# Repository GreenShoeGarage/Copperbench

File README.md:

# COPPERBENCH
### A PCB workbench that feels like a PCB.

**Version 1.7.1 · Green Shoe Garage / Field Instruments · 18 September 2026**

[CaseBench export](docs/CASEBENCH-EXPORT.md) · [Editing and export review](docs/EDITING.md) · [Pan the view](#new-in-v163--pan-the-view) · [Compact polarity](#new-in-v162--compact-polarity-markings) · [Quieter workbench](#new-in-v161--quieter-workbench) · [Modules & circuit blocks](#new-in-v16--modules-and-editable-circuits) · [Controller carriers](#controller-carriers) · [Everyday maker parts](#everyday-maker-parts) · [Polarity & silkscreen fix](#polarity-and-silkscreen) · [Power & ground planes](#power-and-ground-planes) · [Create vias](#create-vias) · [HATs & shields](#hats-shields-and-carriers) · [Get started](#start-here) · [Publish to GitHub](docs/GITHUB.md) · [Deploy](docs/DEPLOYMENT.md) · [Verification](docs/TESTING.md) · [Contribute](CONTRIBUTING.md)

Put down a board. Place recognizable parts. Connect their leads. Shape the copper. Add your markings. Inspect the files you will send for fabrication.

COPPERBENCH is a local-first, two-copper-layer PCB layout app with an editable, depth-rendered 3D workbench. **COPPERBENCH is the working title for this release.** The physical bodies are representative; pad geometry and the electrical connection model—not rendered pixels—drive routing, checking and manufacturing export.

## New in v1.7.1 — CaseBench board JSON

Click the **▾ beside Export board → CaseBench JSON**, or use **Board →
CaseBench JSON**. Review the dimensions and component/hole counts, then choose
**Download CaseBench JSON**. In CaseBench, import it as a CopperBench board.
No upload or service is involved.

The download uses native **`app: "COPPERBENCH"`, schema 5, `units: "mm"`**.
Board shape/thickness, both-side components, local pads, active mounting holes,
slots, cutouts, vias, module/carrier metadata and placed block records are retained.
It does not flatten, move, mirror or rescale the geometry; the CaseBench importer
owns the conversion into enclosure coordinates. Representative module body height
already includes its modeled stack and is not increased again.

The default board snapshot omits artwork, image assets, saved baseline and unused
circuit-block templates. **File contents & options → Include project extras**
retains those too. Keep **Save JSON** for complete editable-project backups.
Unrouted nets or stale copper fills do not block this enclosure handoff. Pending
placement/edit proposals and changes after review do block downloading an obsolete
snapshot. File size and known CaseBench native-adapter bounds are preflighted.

No project-format migration or new runtime dependency. The target CaseBench app
was not available locally for an end-to-end import test; the native contract and
geometry preservation are tested, not physical enclosure fit. See the
[handoff guide](docs/CASEBENCH-EXPORT.md) and [verification record](docs/TESTING.md).

## New in v1.7 — editing and export review

Select the object you intend to edit with **Parts / Copper / Markings / Board
features** filters. Click a crowded location and press **]** to cycle overlapping
objects. Slide trace segments, move/insert/remove corners, replace a section and
clean redundant bends. Widths can target one segment, a trace, touching copper or
an explicitly selected whole net.

Turn on **Drag connected** for a rule-checked component/via move. Supported
centered endpoint attachments follow on their existing layers. A blocked or
unsupported move leaves the original board intact. This is deliberately limited:
no push-and-shove, locked attachments, through-middle junctions or pour-net moves.
Both manual trace changes and connected moves use **Keep edit / Cancel** previews
and one-step undo; they are not live, silent changes to the underlying copper.

**Position marks** moves printed reference or polarity groups without moving pads.
Export review checks actual generated files against the reviewed revision, compares
drills, and reports sampled silk clipping. The ZIP now includes a revision manifest.
Unreadable local saves or detected other-tab changes pause autosave until explicitly
resolved; **Log → Recovery snapshots** can download both copies first.

All **193 parts, six circuit blocks and schema-5 projects** are retained. No new
runtime dependencies. Save a JSON backup before updating; replace the complete
static folder or portable HTML. See the [editing guide](docs/EDITING.md),
[verification record](docs/TESTING.md) and [qualification boundaries](docs/QUALIFICATION.md).
Native browser navigation and the optional third-party parser gate were **blocked**
in the release environment, not counted as passed. No manufacturer acceptance or
physical fabrication is claimed.

## New in v1.6.3 — pan the view

**Pan** now has a labelled button beside **Fit**, in all three views and on both
board faces. Toggle it with **P**, then drag anywhere on the canvas without moving
parts. **Space-drag** or **middle-drag** pans temporarily, including mid-trace.

Scroll pans while Pan is on; Ctrl/Command-scroll still zooms. On a touchscreen,
one finger in Pan or two fingers in any tool moves the view, with pinch zoom
anchored beneath the gesture. **Fit / Home** brings the board back to centre.

Selection, pending placements, unfinished traces, undo history and manufacturing
geometry are preserved. There is no new idle instruction banner, no dependency,
and no project-format change (schema 5). The 193 parts, six circuit starters,
planes, vias and compact printed polarity markings are retained.

[Navigation controls and details](docs/NAVIGATION.md) · [Verification](docs/TESTING.md)

## New in v1.6.2 — compact polarity markings

Removed the always-on A/K billboards and the expanded name badges. The idle
workbench shows the actual small printable symbols. Selection, hovering a lead,
or routing exposes **9-pixel pin tags** placed outside projected component bodies,
including their height when the board is tilted. Full terminal names remain in
the tooltip, inspector and pin table; the small tags still select their actual pins.

**A/K and +/− are real silkscreen**, enabled by default, with 0.9 mm default print
height and 0.16 mm stroke. A direct **Print polarity on silkscreen** checkbox is
available in the selected-part inspector. **Polarity & pin roles → Compact print
defaults → Apply polarity labels** restores the small enabled print settings.
Screen tags and printed sizes are independent. Four-lead RGB LEDs now receive
separate, pin-ordered markings instead of overprinted A/K pairs.

Existing explicit print settings and opt-outs are preserved. Back up your JSON,
inspect **Fabrication → Top silk only / Bottom silk only**, and regenerate the
manufacturing ZIP. Schema remains **5**. No pad, pin number, net, copper, or drill
geometry was changed by the label redesign. Read the [polarity guide](docs/POLARITY_AND_SILKSCREEN.md)
and [verification record](docs/TESTING.md). The [example board](examples/compact-polarity.json)
is an unconnected illustration, not a complete circuit.

## New in v1.6.1 — quieter workbench

The board is the focus. Removed the welcome overlay, canvas slogans, repeated
instructions and duplicate empty-inspector statistics. Search is first in the
parts drawer; a category selector replaces the filter-chip wall, and compact
catalog buttons replace long promotional labels. Additional block and footprint
actions live under **Library tools**.

The idle Select tool has no instructional sentence. Active tools display a short
next-step hint; the **?** beside the tool name opens complete instructions without
cancelling the operation. Header **?** or **H** opens the full guide and shortcuts.
Autosave, polarity, error/warning counts, clearance failures, confirmation dialogs
and fabrication-export gates remain visible and operational. Native schema 5,
the 193 parts and all six circuit blocks are unchanged.

**Upgrade:** save a JSON backup and replace the complete hosted app folder, or
replace the standalone HTML. No new schema migration is needed for v1.6 projects.
See the [interface guide](docs/QUIET_WORKBENCH.md) and [verification record](docs/TESTING.md).

## New in v1.6 — modules and editable circuits

**Five specific module interfaces and six reusable circuit starters.** The component
library now has **193 entries**; circuit blocks are a separate collection of editable
parts, copper and net intent—not six opaque additional footprints.

| Mount a purchased module | Build and edit a circuit |
|---|---|
| Adafruit BME280 original non-QT, DS3231 original eight-pin RTC, 0.96-inch OLED STEMMA QT, TB6612 breakout, and MPM3610 3.3 V module. | LED indicator, button with pull-up, I²C pull-ups, supply decoupling, DC-input topology, and RC signal filter. |
| Named pins, source CAD/blob references, optional mounting holes, adjustable assumed underside gap, and distinct representative 3D bodies. | Pre-routed internal copper, editable values, explicit external ports, fresh nets per insertion, one-step undo, group transforms and fresh-net copies. |

Open **Parts → Modules** or **Parts → Circuit blocks**. Module templates
place the mating headers on your carrier; the illustrated host electronics do not
leak into fabrication files. Block placement checks for new copper conflicts while
preserving intentionally unrouted connections as design findings.

Select a block member to **select the whole block, move/rotate/flip it with its
copper, copy it with fresh nets, export it, or detach the grouping**. Save selected
components/traces/vias to a project-local personal library; import and export
`.copperblock.json` files for sharing. GND is not silently shared between copies.

**Back up first. Native JSON now writes schema 5**, reading schemas 1–4 without
replacing existing embedded footprints. Older app versions reject the new format.
Source-referenced module interfaces and circuit examples are **not physically fit
tested, simulated or electrically certified**. KiCad retains ordinary supported
geometry/nets, not module metadata, block grouping or your personal library.

[Module and block guide, source ledger and limits](docs/MODULES_AND_BLOCKS.md) ·
[Verification](docs/TESTING.md) · [Compatibility](docs/COMPATIBILITY.md)

## Controller carriers

**v1.5 added 18 header-mounted interfaces for nine host selections; all are retained.** Start with **Parts → Controllers** or use
**Examples → Controller carriers**. Choose Pico, Pico 2, Pico W, Pico 2 W, classic
Nano A000005, ESP32-DevKitC V4 with WROOM-32E, the classic Feather interface,
original XIAO RP2040 or XIAO ESP32C3. Each has a carrier and an add-on variant;
Feather's add-on is a FeatherWing-style mating pattern.

**Carrier clearances & fit** edits the assumed stack gap, USB/access projections,
and attached two-face antenna guards where applicable. Copper guards affect
manual routing, vias, automatic routing and plane fills. They follow moves,
rotations and flips; hiding their overlay never disables them. A guard override
requires a saved reason and remains a warning. XIAO ESP32C3 uses an external
antenna reference; generic Feather cannot imply a radio-specific keepout.

The footprint contacts are routable, named and included in manufacturing exports.
Host drawings and clearance overlays are editor-only. Optional mounting holes
are real NPTH geometry; ESP32 and XIAO do not receive invented holes. Existing
parts, optional Uno ICSP, vias, planes, polarity labels and repaired silk exports
are retained.

**These are nominal source-referenced templates, not fit-tested assemblies.**
The RF defaults are suggested projections, not complete manufacturer-qualified
clearances. Header-to-edge offsets, holes, connector drill size, stack gap and
cable access require actual-board review. The generic Feather entry provides
common aliases, not universal MCU pin mappings. Direct castellated mounting is
not included. See the [carrier guide and source/geometry qualifications](docs/CARRIERS.md).

**Native JSON now writes schema 5; older editors will reject it.** Schemas 1–4
open without silently replacing embedded footprints. Back up before upgrading.
KiCad exports active RF guards as independent keepouts, not linked constraints;
retain JSON as the lossless master. [18 starter projects](examples/carriers/) are
included. These starters are interfaces, not complete functioning circuits.

## Everyday maker parts

**v1.4 adds 134 variants in 17 families, for 170 total library entries at that release.** Choose
**Parts → Maker parts**, select a family and exact variant, and place it
on the board. The drawer groups variants instead of listing hundreds of similar
cards; search finds device names, manufacturers and pin functions directly.

Connectors include header/socket/right-angle variants, screw terminals, JST
PH/XH/SH, a Qwiic/STEMMA QT preset, and a selected GCT USB4085 USB-C connector.
Controls include switches, potentiometers and an encoder. Power/assembly entries
include regulators, protection templates, transistors, a relay, fuses, LEDs,
jumpers and test loops. Named NE555, LM358, SN74HC595, MCP23017 and ULN2803C package
entries expose actual pin functions instead of anonymous pad numbers.

**Functional pin names** edits labels without changing pin numbers or nets.
Selected parts show editor-only captions; existing A/K and +/− polarity symbols
remain real printed silkscreen. **Part reference, notes & pin-map CSV** exposes
source links, cautions and review status. Internally common terminals assigned to
different nets produce a blocking finding—not an automatic merge.

**Arduino Uno R3 now has an optional ICSP 2×3 header.** Enable it in the platform
chooser or on an existing Uno part. Its six contacts are appended without changing
the original 32 pins or connections. Existing default templates stay unchanged.

**Important:** 134 variants does not mean 134 physically qualified purchased
components. Some entries are named-device references; others are explicitly
nominal parametric templates. Review the exact part, geometry, connector direction,
pin mapping and drill/slot capability before fabrication. USB connectors and
regulators are parts, not complete supporting circuits. No physical fit or
manufacturer approval is claimed.

Try **Examples → Everyday maker sampler**, or open
[`everyday-maker-sampler.json`](examples/everyday-maker-sampler.json). The example
is a layout sampler, not an electrically complete circuit. See the
[Maker Parts guide](docs/MAKER_PARTS.md) and [catalog index](docs/MAKER_CATALOG.md).
v1.6 uses schema 5 and retains these embedded footprints and checks. Back up before upgrading.

## Polarity and silkscreen

**v1.3.1 fixes an export defect that could clear the entire silkscreen. Open your
native project in this version and regenerate its manufacturing ZIP before
ordering. Previously downloaded Gerbers are not repaired by updating the app.**

Diodes and LEDs now identify **A · Anode** and **K · Cathode**. Polarized radial
capacitors identify **+ · Positive** and **− · Negative**. Small tags appear while
selecting or wiring, stay outside projected component bodies, and never expand
into full-name badges. Full names remain in tooltips, the inspector and pin table.

Select a component and open **Polarity & pin roles** to assign roles to custom or
imported pins, toggle printing, or adjust symbol size, clearance and offsets.
Printed A/K or +/− symbols follow the component's rotation and board face and are
included in the Gerbers. Hiding the reference label does not hide polarity marks;
disabling printed polarity does not remove the contextual pin tags. No operation
silently swaps pin numbers or reassigns nets. Unknown/numeric pin roles are not
guessed from net names or body appearance.

**Fabrication → Top silk only / Bottom silk only** shows the generated files
without component bodies or editor badges. Source text, part references,
polarity marks, drawing tools and converted images survive export, while pad
openings, holes, cutouts and off-board artwork are still cleared.

The old writer incorrectly treated nested Gerber contours like an even-odd hole.
The old viewer and Python test reader repeated that error. All three are fixed;
new tests explicitly reproduce the blank old output and require union semantics.
The clipping replacement uses individual exterior trapezoids, not another nested
frame. See the [fix guide](docs/POLARITY_AND_SILKSCREEN.md) and
[verification record](docs/TESTING.md). **No external CAM acceptance or physical
fabrication is claimed.** v1.6 writes schema 5; save a JSON backup first.

## Start here

**The simplest edition is `COPPERBENCH-portable.html`.** Open that file in a desktop browser. It includes the complete app, component definitions, ZIP support and routing/checking worker source. There is no build step, account, CDN or required internet service.

Alternatively, keep the static app folder together and open `index.html`. A local server is useful where browser file-origin policies interfere with local storage or workers:

```sh
cd copperbench
python3 tools/serve.py
```

Open `http://127.0.0.1:8000/`. Python is optional for using the portable HTML. Node and Python test dependencies are only needed for development/testing.

**Save JSON is your independent backup.** Autosave uses browser-local storage, which can be disabled, full, cleared, or unavailable for local files. A saved-state LED reports persistence status; a failed save does not disable JSON export. Downloaded JSON contains placed footprints and embedded source images.

The release uses a real Chromium DOM/canvas/worker harness with a storage test double and intercepted download blobs. Unrestricted `file://` launch, origin-backed storage, actual download navigation, and hosted service-worker installation were **not** directly verified. Read the [verification record](docs/TESTING.md) for exact coverage instead of treating “offline-capable” as a claim that every browser environment has been tested.

## Power and ground planes

Open **Planes → Bottom ground · top routing**. Or assign a net independently to
**Top copper** and **Bottom copper**. No whole-board polygon drawing is needed.
The plane follows the outline and automatically refills after copper edits.

Choose **Connect a lead to GND** (or your selected net), click a component lead,
then review **Keep connection / Discard**. Through-hole and same-face pads use
existing direct contact when possible. Opposite-face surface-mount pads receive
a short trace and nearby through via, or reuse a suitable existing via. Inspector
pin buttons and picked multi-lead groups expose the same workflow.

**No silent net merges.** Unassigned leads adopt the target net only on acceptance;
a lead on a different net is blocked. Connection status uses real filled-copper
paths, not names. Split planes, stranded leads and stale fills remain visible.
Changing plane assignment does not relabel pins or existing copper. Manual zones
are preserved. New traces carve clearance through managed pours and may split them.

Thermal pad connections, solid via connections, per-face settings, a view-only
hide-fill control, manual refill and one-step undo are included. The local helper
is non-exhaustive and the existing fill engine is conservative/cell-derived.
**Native saves use schema 5 in v1.6; back up older projects before upgrading.**

[Plane workflow and limitations](docs/PLANES.md) · [Verification](docs/TESTING.md)

## Create vias

Click **＋ Via** beside the trace-width control, choose **Place via** in the Nets
panel, or press **Shift+V**. The inspector shows the via's net, copper-pad diameter,
drill diameter and solder-mask setting. Click the board to place; keep clicking
to place more. **Esc** leaves the tool.

**Auto / from touching copper** takes the net from the copper beneath the via,
including the opposite face. A placement joining different nets is blocked.
For an empty area, choose a named net or create one. Unassigned vias remain
editable but produce a blocking finding before ordinary manufacturing export.
The green/red preview checks the selected rule profile on both copper layers.

| Preset | Copper pad diameter | Drill diameter |
|---|---:|---:|
| Compact | 0.70 mm | 0.30 mm |
| Standard | 0.90 mm | 0.40 mm |
| Large | 1.20 mm | 0.60 mm |

Enter custom dimensions as needed. Presets are geometric conveniences, not
current ratings or universal fabrication approval. The inspector displays the
annular ring and rejects dimensions below the active profile limits.

**During manual tracing**, press **V** at the cursor, or click **Via → other side**
and then the board. The incoming trace and via are one undoable edit, and the
route continues on the opposite layer. A rejected placement leaves the trace
and board unchanged. Traces can start or finish on existing vias and copper.

**To edit**, leave placement mode and select the via—even at a trace endpoint.
Change its position, net, diameters, mask coverage or lock state. **Manage vias**
in the Nets panel lists all vias. Moving a connected via does not stretch the
attached traces; resulting disconnections are reported.

A via is real copper on **both faces** and **one plated Excellon drill**, not an
NPTH mounting hole. **Tent both sides** omits its solder-mask openings on both
faces; it does not request hole filling or guarantee a physically sealed hole.
Native JSON preserves all settings. The bounded KiCad exchange preserves via
geometry/nets, but not per-via tenting or locks; the app warns before that export.

See the [via guide](docs/VIAS.md), [format limits](docs/COMPATIBILITY.md), and
[verification record](docs/TESTING.md). No manufacturer upload or physical test
board is claimed for this release.

## HATs, shields and carriers

**Parts → HATs & shields** opens the new form-factor workflow. Select
Raspberry Pi 40-pin, Arduino Uno R3, or Arduino MKR 28-pin; choose an add-on above
the host or a carrier below it. **Start new board** creates an outlined blank
with the mating pattern and optional mounting holes. **Place headers on current
board** adds only the interface, preserving your existing layout.

There are **six new Parts → Platforms entries**, one add-on and one carrier
variant per family. Pins are directly routable, with physical contact IDs and
signal aliases in the inspector, hover tooltip and searchable pin table. No pins
are silently joined just because their signal names match. Export a pin-map CSV
from the selected interface's inspector.

| Family | Included geometry | Important boundary |
|---|---|---|
| Raspberry Pi 40-pin | 2×20 connector; physical/BCM aliases; 65×56 mm legacy-style add-on blank; four optional mounts | Not Pico, Compute Module, original 26-pin Pi, or automatic HAT/HAT+ compliance. |
| Arduino Uno R3 | All 32 perimeter contacts; grouped banks; exact 4.064 mm D8–D7 gap; classic-outline starter | ICSP 2×3 is optional. Not a blanket Uno R4 / clone compatibility claim. |
| Arduino MKR 28-pin | Two 14-pin rows; 2.54 mm pitch; 20.32 mm row spacing; shield and carrier roles | WiFi 1010 reference envelope/nominal offsets. Check the actual MKR variant, antenna and power pins. |

The compound pattern starts **locked** in a new template. Uncheck **Lock placement**
in the inspector to move, rotate or flip it. Its included mounting holes move
with it. **Host reference & mounting holes** toggles the reference illustration,
editor-only captions and real NPTH holes independently. The host picture is not
a collision/clearance model and does not export fake host circuitry.

All dimensions are **nominal, review-required**. Check the purchased connector,
actual host, standoffs, power direction and clearances. See the detailed
[form-factor reference and source register](docs/FORM_FACTORS.md).

**Project format:** v1.6 reads schema-1/2/3/4 projects and writes schema 5. Older apps
reject the new schema instead of silently dropping block records or attached carrier constraints.
Keep the original JSON backup before upgrading. Native JSON preserves platform
aliases, linked mounting holes and plane behavior. KiCad subset exchange retains
supported geometry, not all application metadata.

## Try the complete workflow

1. Open **Examples → Little light**, or open `examples/little-light-routed.json` to inspect the completed routing example. Choose **Fresh start** for an empty board.
2. In **Parts**, click a part and click the board, or drag it from the drawer. **R** rotates; **F** moves the selected component to the opposite face. The inspector has exact position, angle, value and pin assignments.
3. Choose **Connect** (**A**), pick two or more leads belonging on one net, then choose **Preview wire → Keep copper**. Copper is not committed until accepted. Different-net assignments require an explicit merge decision. **Pair connectors** creates separate mapped connections instead of shorting an entire selection together.
4. Choose **Trace** (**T**) for manual routing. Set the visible trace width, click a lead, via or existing trace, add waypoints and click the destination. **V** inserts a through via at the cursor during a route, switches to the opposite layer and continues. The visible **Via → other side** button instead arms the next click. **Enter** finishes an open route; **Esc** cancels unfinished work.
5. Use **Board** to adjust size/shape, draw polygon boundaries, add mounting holes, slots or cutouts. Resizing changes the boundary, never the dimensions of parts or copper.
6. Use **Mark** for text, lines, boxes, ellipses or image conversion. Imported raster/SVG images become explicit silkscreen rectangles, with the source raster retained for reprocessing. Use **Check design**, then **Fabrication**, then **Export board**. Review the actual manufacturer preview before ordering.

For easy whole-board pours, use **Planes**. For manual local pours, draw a **Zone** (**Z**), assign its net and refill. Zones use conservative, vectorized cell fills, with optional thermal reliefs and island removal. Copper/board edits and project imports invalidate pours; stale pours block manufacturing export, even when diagnostic export is selected.

## Established workbench features

| Area | Implemented |
|---|---|
| Physical workbench | Shaded, depth-buffered representative 3D bodies; tilt, orbit, zoom, pan, top/bottom views, x-ray and pin picking. |
| Parts | 193 entries including five module interfaces, 18 controller interfaces and 134 maker variants, named device pins, source notes, optional Uno ICSP, footprint wizard, exact pad editing in Advanced mode, rotate/flip, duplicate, lock, pin table. |
| Circuit blocks | Six routed starters, explicit external ports, isolated-net insertion/copy, editable members, group transforms, project-local library and standalone block JSON. |
| Modules | Five source-identified mating interfaces with named pins, optional mounting holes, reference-only 3D bodies and nominal stack-gap review. |
| Carriers | Nine added host selections, carrier/add-on templates, attached two-face RF guards, access references and editable stack-gap assumptions. |
| Connection intent | Explicit nets independent of drawn copper, visible unrouted connections, guarded net merges, connector-pair mapping. |
| Routing | Width-controlled manual polylines, selected two-/multi-pin A* proposals, keep/reject preview, through vias, cancellable worker jobs. |
| Vias | Visible repeat-placement tool, net inheritance, pad/drill presets and exact sizes, mask tenting, live clearance checks, editable/lockable objects and a management table. |
| Planes | Per-face net assignment, bottom-ground preset, board-following auto-refill, checked lead-to-plane previews, local stub/via helpers, real-region status and split-plane findings. |
| Board/copper | Rectangular, rounded, circular/elliptical and polygon outlines; polygon cutouts/keepouts; holes/slots; thermal and solid cell-derived copper fills. |
| Markings | Drafting text, basic shapes, mirror/rotate, threshold/invert/cleanup image conversion, original-image reprocessing, minimum-feature and clipping warnings. |
| Inspection | Geometry/connectivity findings with severity and evidence, footprint-verification flags, assumptions/evidence register, baseline comparison, HTML/print review report. |
| Files | Native JSON/project ZIP, Gerber X2 or RS-274X compatibility output, Excellon drills/G85 slots, optional paste, BOM CSV, SVG output, bounded KiCad interchange. |
| Workspace | Undo/redo, autosave and recovery snapshots, Easy/Advanced modes, light/dark/high-contrast themes, collapsible drawers/inspector, responsive layout. |

**Bench, Copper and Fabrication are views of one design.** The Fabrication view reads the generated Gerber/Excellon text rather than redrawing the project and calling that verification.

## Manufacturing: inspect before ordering

Export produces front/back copper, mask and silkscreen, an outline/cutout Gerber, and the applicable plated/non-plated drill files. Optional paste layers are available. Coordinates share one physical origin; bottom manufacturing files are not mirrored. The native editor uses millimetres and a top-left, Y-down coordinate system; export converts Y to a lower-left, Y-up system.

An editable OSH Park two-layer rule profile is included with its source and verification date. Manufacturer limits can change. Confirm the selected service, current rules, upload interpretation and preview before placing an order.

**This release has not been submitted to OSH Park, checked by an external CAM product, or physically fabricated.** Its exports passed JavaScript read-back and a separate Python/Shapely geometry regression for a golden test coupon. That is useful evidence, not manufacturer approval or a guarantee that an arbitrary circuit will work.

Generic footprints are marked **unverified** until you check the purchased part's mechanical drawing, pin order and recommended land pattern. Width presets are dimensions, not current ratings. A zero-error layout is not a circuit-function, high-voltage, RF, thermal or regulatory certificate.

## Deliberate boundaries

This is not a complete replacement for an industrial EDA suite. Two copper layers and through vias are supported; multilayer stackups, blind/buried vias, simulation, controlled impedance and push-and-shove routing are not. Automatic routing is selected-connection assistance, not guaranteed full-board optimization. Moving a part leaves existing copper in place and exposes any resulting broken connections.

Copper pours are cell-derived vector rectangles, not a general exact polygon-boolean engine. Arcs imported from KiCad are flattened to polylines. Representative component bodies are not STEP models or mechanical collision certification. The silkscreen alphabet is a bundled geometric drafting alphabet rather than arbitrary typography.

KiCad import/export is an **explicit feature subset**, not general round-trip compatibility. Important unsupported manufacturing features stop import; permitted simplifications are reported. Imported board artwork is flattened; standalone footprint placement imports pads/body, not original footprint artwork. External 3D assets are not fetched. See [format compatibility](docs/COMPATIBILITY.md).

## GitHub-ready repository

Extract the source ZIP and put the **contents of the `copperbench` folder** at
your repository root. Include hidden files and folders. There is no preconfigured
remote, account name, domain, Git history or secret in the package.

The repository includes an illustrated README, MIT and dependency notices,
contribution/security guides, issue and pull-request templates, pinned test
dependencies, a lockfile, source integrity checks, deterministic release
packaging and three GitHub Actions workflows:

| Workflow | Behavior |
|---|---|
| **CI** | Source/asset checks, packaging regressions, engine tests, independent manufacturing geometry and the Chromium interaction harness. |
| **Deploy GitHub Pages** | Manual deployment after Pages setup; optional automatic deployment from `main` with `ENABLE_PAGES=true`. |
| **Draft release** | A matching pushed version tag creates a draft with source/static ZIPs, portable HTML and SHA-256 checksums after CI. |

[GitHub setup](docs/GITHUB.md) explains the initial push and release tags.
[Deployment](docs/DEPLOYMENT.md) covers local launch, Pages and an ordinary static
host. These workflow files are prepared locally; no remote Actions run or live
site is claimed.

```text
copperbench/
├── index.html                 Ready-to-run static entry point
├── COPPERBENCH-portable.html   Self-contained offline edition
├── styles.css                 Responsive themes and layout
├── src/                       PCB model, geometry, renderer, UI and exporters
├── vendor/                    Bundled JSZip and its original license
├── examples/                  Starter designs and regression coupon
├── docs/                      Screenshots, compatibility, guides and evidence
├── tests/                     Engine, browser, manufacturing and packaging tests
├── tools/                     Serve, check, test, rebuild and package commands
├── .github/                   CI, Pages, release and issue/PR templates
├── package.json               Optional npm command shortcuts
├── requirements-dev.txt       Test-only Python dependencies
├── LICENSE                    Original MIT license
└── README.md                  This guide
```

## Developer commands

No dependency installation or compilation is required to use the shipped app.
For development, use Node.js 22+ and Python 3.13. Install test dependencies in a
virtual environment; the full setup is in [testing](docs/TESTING.md).

```sh
python3 tools/serve.py            # Local app at 127.0.0.1:8000
python3 tools/package.py          # Rebuild portable HTML, worker and offline cache
python3 tools/package.py --check  # Verify generated assets without writing
node tests/core.test.js           # Run engine tests; generate test-only coupon
node tests/platforms.test.js      # Platform geometry and export fixtures
node tests/vias.test.js           # Via rules, connectivity, mask and drill fixtures
node tests/planes.test.js         # Plane attachment, real connectivity and export fixtures
python3 tools/test.py             # Run all suites (requires test dependencies)
python3 tools/release.py          # Source ZIP, static ZIP, portable HTML, checksums
```

On Windows, use `py -3` in place of `python3`; the direct Python commands avoid
assuming a particular shell. npm shortcuts are optional and use `python3`.
`npm test` needs Node only; there are no npm dependencies to install.

New results, screenshots and generated fixtures go to ignored `tests/output/`.
They do not rewrite the checked-in examples or documentation images. The browser
runner uses Playwright's installed Chromium by default; `CHROMIUM_EXECUTABLE`
provides an explicit local override. Current test output records actual run times.

After changing runtime source, rebuild and commit the generated files. The
service-worker cache revision is content-derived and scoped to its deployment
path; manual cache-counter edits are unnecessary. Hosted cache lifecycle remains
outside the embedded browser harness's coverage.

See [the roadmap](docs/ROADMAP.md), [architecture](docs/ARCHITECTURE.md),
[release notes](docs/RELEASE_NOTES.md), [changelog](CHANGELOG.md),
[format/profile references](docs/SOURCES.md) and [compatibility](docs/COMPATIBILITY.md).

## License

Original application code is distributed under the MIT license; see `LICENSE`. JSZip 3.10.1 is redistributed under its MIT option with its original license in `vendor/JSZIP-LICENSE.md`. The app uses system UI fonts and its own geometric stroke alphabet; no external font files, component model library, KiCad library bundle, telemetry or remote asset service is included.

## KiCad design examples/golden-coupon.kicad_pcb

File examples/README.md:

# Example boards and test files

These are editable software demonstrations, not manufacturer-approved reference designs.

- `everyday-maker-sampler.json`: unconnected layout of 14 representative v1.4 parts. It is a visual/layout demonstration, not a complete circuit.
- `uno-r3-shield-icsp.json`: Uno shield interface with six optional main-MCU ICSP contacts appended to the original 32 perimeter contacts. Check the physical host and mating connectors.
- `polarity-and-silkscreen.json`: visual software proof of diode/LED/capacitor role labels, both-face text, drawings and filled image geometry. It is not a working circuit.
- `power-ground-planes.json`: small software fixture with top +5V and bottom GND pours, a through-hole ground seed and a surface-mount ground attachment through a short trace and via. Imported pours refill automatically. This is a geometry demonstration, not a powered circuit.
- `starter.json`: small through-hole learning board with explicit nets to route.
- `little-light-routed.json`: that board routed through the actual browser interface during release testing; no blocking geometry findings in that exercised state. Its generic parts still require datasheet verification.
- `smd.json`: surface-mount layout exercise.
- `mixed.json`: mixed through-hole/SMD and two-face exercise.
- `golden-coupon.json`: 40 × 30 mm geometric regression fixture with top, bottom and via-linked nets, through pads, one NPTH round hole, one NPTH slot and text.
- `golden-coupon.kicad_pcb` and `golden-fabrication/`: generated interchange/manufacturing files for that regression fixture.

The golden coupon's `verified` part flag identifies controlled **software test geometry**, not a certification against a particular purchased component. It is labelled as a software fixture in its evidence record. No example has been physically fabricated or submitted to a manufacturer as part of this release.

Regression suites write new fixtures, files and screenshots under ignored `tests/output/`, not these checked-in examples. IDs in test outputs may change without changing their geometric purpose.

The golden manufacturing files were regenerated with v1.3.1 to remove the old
silkscreen clear-frame defect. Re-export any older manufacturing ZIPs; see
[the correction guide](../docs/POLARITY_AND_SILKSCREEN.md).

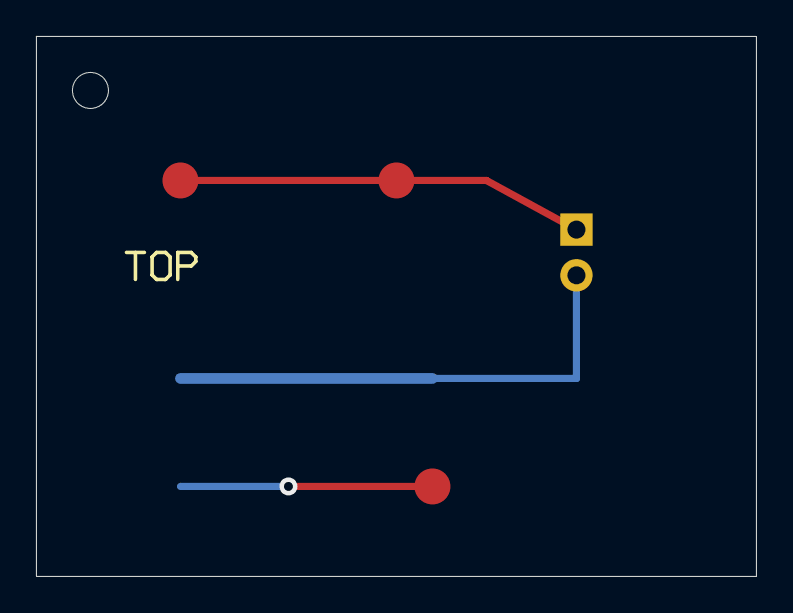
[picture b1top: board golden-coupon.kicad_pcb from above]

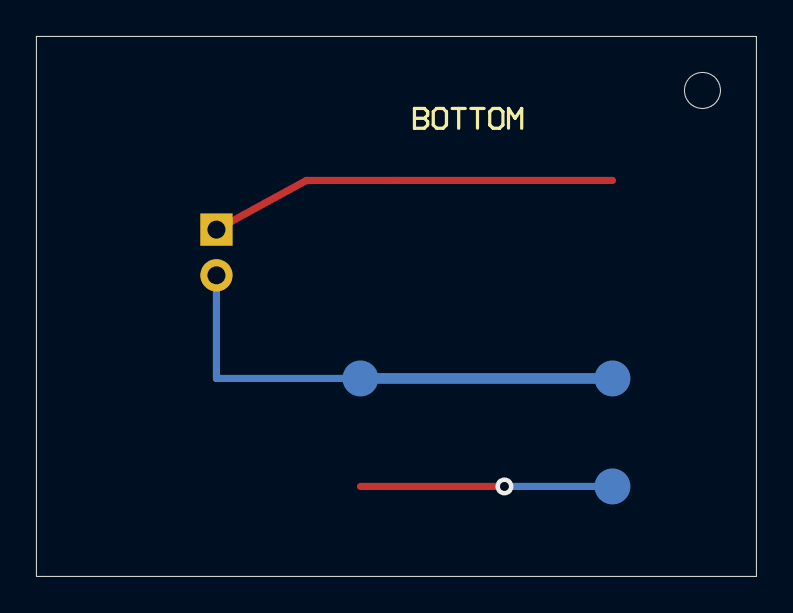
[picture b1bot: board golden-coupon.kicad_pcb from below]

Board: 2 copper layers, 40.0 x 30.0 mm, 7 parts (3 on the bottom side), 3 nets.

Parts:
J1: 1×2 / 2.54; Header · 1 × 2
TP1, TP2, TP3, TP4, TP5, TP6: Test point; Test point · 2 mm

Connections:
BOTTOM_LINK: J1.2, TP3.1, TP4.1
TOP_LINK: J1.1, TP1.1, TP2.1
VIA_LINK: TP5.1, TP6.1
